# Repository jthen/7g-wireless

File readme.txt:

I've added a few things since my last update.

The first is the ability to "play" a text string as keystrokes on the receiver. So, the keyboards sends the string "this is a message" to the receiver which is then translated into keystrokes. These keystrokes are then sent to the PC as if the user typed "this is a message".

I used this to build a menu system which at the moment is used to set the brightness of the LEDs and the output power of the transmitter. Pressing Func+Esc enters the menu and this is what it currently looks:

[code]
7G wireless
firmware build Jul 30 2013  13:38:18
battery voltage=2.83V
keyboard's been on for 0days 21hour 39min 10sec

what do you want to do?
F1 - change transmitter output power (current 0dBm)
F2 - change LED brightness (current 1)
Esc - exit menu
[/code]
Pressing F1 or F2 then opens a sub-menu which allows changing these values.

The menu shows the current battery voltage. This needs a little tweaking to be more accurate, but it serves it's purpose at the moment. In the next PCB revision, I want to improve the circuit which measures the voltage. I have to dig into the AVR datasheets and look for some examples.

The firmware also has a clock (watch) which starts when the keyboard receives power. That's the "keyboard's been on for..." part of the menu. This clock is used in the sleep system (see below), but can be used as a real clock too.

There is also a LED "driver" thing which allows sequences to be replayed. So, for instance, I can play an LED sequence where 1 LED is on for a while, then 2, then all three. The driver also allows gradual transitions from bright do dim and back, but this still needs some testing, I think there are bugs in it. This can be used for all sorts of indicators.

The bad news: transmitter range sucks! On highest transmitter output power (0dBm) I get a range of 6-8 meters, and on the lowest I get 1-2 meters tops. I've used these modules for other projects, and I've confirmed a range of at least 60 meters. The chip should also be able to send a signal through at least one wall, which is not the case now. This, of course, means there is something wrong. I don't know what causes these, but I'm guessing either the keyboard PCB or my controller PCB are somehow shielding the transmitter. Tests are needed...

I don't do any frequency hopping. The channel is hard-coded at the moment. The transmitter will to re-send the package for for a number of times, or until it gets an acknowledge from the dongle.

The controller does not have any reverse voltage protection. So, reversing the batteries will probably fry the entire circuit. I will have to add this in the next controller revision.

The firmware doesn't do any encryption of the data it sends. This means that it's not too hard to build a circuit that can "listen" and log keystrokes. This can be fixed, of course, but it's not very high on my priority list. I'm not very paranoid...

The firmware puts the keyboard into sleep for a variable duration of time which depends on the time since the last change of the state of the keys. The idea is that while the user is typing, this sleep time will stay relatively short (say, 4ms) and if the user is not typing this interval will gradually increase to a max value (at the moment 71ms). Then, as soon as the user starts typing again, the sleep duration will jump back to the minimal value. Currently the implementaion of this is very crude, and needs more work. I plan to make this configurable so that the user can select if he wants to save power with longer sleeps, or have a more responsive keyboard and drain the batteries quicker. I also thought about making a "deep sleep" mode which puts the keyboard in a state where it will sleep for longer durations (say, 500ms) between matrix scans and wait for a specific key combination to get out of this deep sleep. The idea here is that you want to put the keyboard in deep sleep if you want to transport it, or if you want to lock it. The keyboard could also go into deep sleep if no keys have been pressed for a long time (30 minutes or so) to preserve power.

Because of this sleep system I decided I will not do any debouncing. What's the point of debouncing if I'm already scanning the keyboard matrix every 4ms or longer? Any comments on this?

The source code and the Eagle CAD schematics of the controller PCB are on:

https://code.google.com/p/7g-wireless/

So, that's it for now.

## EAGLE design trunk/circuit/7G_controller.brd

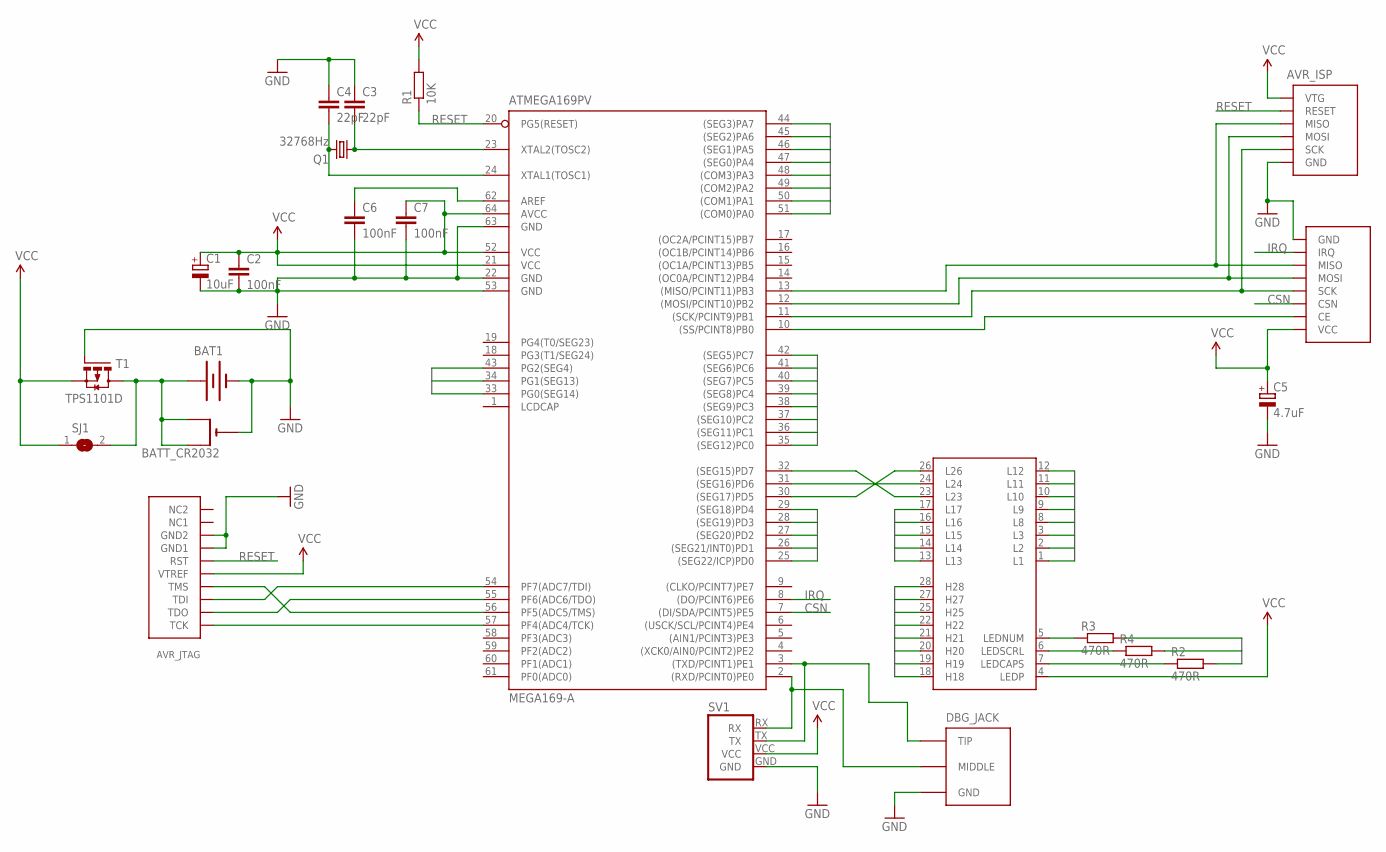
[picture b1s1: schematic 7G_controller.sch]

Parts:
ATMEGA169PV: MEGA169-A; TQFP64
AVR_ISP: AVR-ISP-6SMALL_FP; AVR-ISP-6-SMALL-FP
AVR_JTAG: AVR-JTAG
BAT1: BATTERYPLAIN; BATTERY
BATT_CR2032: CR2032SMT; CR2032-SMD
C1: 10uF; SMC_B
C2, C6, C7: 100nF; C0805
C3, C4: 22pF; C0805
C5: 4.7uF; SMC_B
DBG_JACK: JACK_FEMALE_3.5MMCHEAP; JACK_CHEAP
MTRX_CONN: SS7G_CONNSMD; SS7G_CONN_SMD
NRF24L01: NRF24L01_MOD_NINE_EAGLESGENERIC; NRF24L01_MOD_GENERIC
Q1: 32768Hz; NSK_QUARTZ_CLOCK
R1: 10K; R0805
R2, R3, R4: 470R; R0805
SJ1: SJ
SV1: UART_PORT
T1: TPS1101D; SO8

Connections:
AREF: ATMEGA169PV.62 (AREF), C6.1
CAPS: ATMEGA169PV.43 (PG2(SEG4)), R2.2
CE: ATMEGA169PV.10 ((SS/PCINT8)PB0), NRF24L01.CE
CSN: ATMEGA169PV.7 ((DI/SDA/PCINT5)PE5), NRF24L01.CSN
GND: ATMEGA169PV.22 (GND), ATMEGA169PV.53 (GND), ATMEGA169PV.63 (GND), AVR_ISP.GND, AVR_JTAG.P$2 (GND1), AVR_JTAG.P$10 (GND2), BAT1.-, BATT_CR2032.-, C1.-, C2.2, C3.1, C4.1, C5.-, C6.2, C7.2, DBG_JACK.1 (GND), NRF24L01.GND, SV1.GND, T1.4 (G)
H18: ATMEGA169PV.42 ((SEG5)PC7), MTRX_CONN.18 (H18)
H19: ATMEGA169PV.41 ((SEG6)PC6), MTRX_CONN.19 (H19)
H20: ATMEGA169PV.40 ((SEG7)PC5), MTRX_CONN.20 (H20)
H21: ATMEGA169PV.38 ((SEG9)PC3), MTRX_CONN.21 (H21)
H22: ATMEGA169PV.36 ((SEG11)PC1), MTRX_CONN.22 (H22)
H25: ATMEGA169PV.35 ((SEG12)PC0), MTRX_CONN.25 (H25)
H27: ATMEGA169PV.37 ((SEG10)PC2), MTRX_CONN.27 (H27)
H28: ATMEGA169PV.39 ((SEG8)PC4), MTRX_CONN.28 (H28)
IRQ: ATMEGA169PV.8 ((DO/PCINT6)PE6), NRF24L01.IRQ
L1: ATMEGA169PV.50 ((COM1)PA1), MTRX_CONN.1 (L1)
L2: ATMEGA169PV.48 ((COM3)PA3), MTRX_CONN.2 (L2)
L3: ATMEGA169PV.46 ((SEG1)PA5), MTRX_CONN.3 (L3)
L8: ATMEGA169PV.45 ((SEG2)PA6), MTRX_CONN.8 (L8)
L9: ATMEGA169PV.44 ((SEG3)PA7), MTRX_CONN.9 (L9)
L10: ATMEGA169PV.25 ((SEG22/ICP)PD0), MTRX_CONN.10 (L10)
L11: ATMEGA169PV.26 ((SEG21/INT0)PD1), MTRX_CONN.11 (L11)
L12: ATMEGA169PV.27 ((SEG20)PD2), MTRX_CONN.12 (L12)
L13: ATMEGA169PV.28 ((SEG19)PD3), MTRX_CONN.13 (L13)
L14: ATMEGA169PV.29 ((SEG18)PD4), MTRX_CONN.14 (L14)
L15: ATMEGA169PV.51 ((COM0)PA0), MTRX_CONN.15 (L15)
L16: ATMEGA169PV.49 ((COM2)PA2), MTRX_CONN.16 (L16)
L17: ATMEGA169PV.47 ((SEG0)PA4), MTRX_CONN.17 (L17)
LEDCAPS: MTRX_CONN.7 (LEDCAPS), R2.1
LEDNUM: MTRX_CONN.6 (LEDSCRL), R4.1
LEDSCRL: MTRX_CONN.5 (LEDNUM), R3.1
MISO: ATMEGA169PV.13 ((MISO/PCINT11)PB3), AVR_ISP.MISO, NRF24L01.MISO
MOSI: ATMEGA169PV.12 ((MOSI/PCINT10)PB2), AVR_ISP.MOSI, NRF24L01.MOSI
unnamed: ATMEGA169PV.32 ((SEG15)PD7), MTRX_CONN.23 (L23)
unnamed: BAT1.+, BATT_CR2032.+$1 (+), BATT_CR2032.+$2 (+1), SJ1.2, T1.5 (D), T1.6 (D), T1.7 (D), T1.8 (D)
unnamed: ATMEGA169PV.23 (XTAL2(TOSC2)), C3.2, Q1.1
unnamed: ATMEGA169PV.24 (XTAL1(TOSC1)), C4.2, Q1.4 (2)
unnamed: ATMEGA169PV.30 ((SEG17)PD5), MTRX_CONN.26 (L26)
unnamed: ATMEGA169PV.31 ((SEG16)PD6), MTRX_CONN.24 (L24)
unnamed: ATMEGA169PV.2 ((RXD/PCINT0)PE0), DBG_JACK.4 (MIDDLE), SV1.RX
unnamed: ATMEGA169PV.3 ((TXD/PCINT1)PE1), DBG_JACK.2 (TIP), DBG_JACK.3 (TIP), SV1.TX
NUML: ATMEGA169PV.33 (PG0(SEG14)), R3.2
RESET: ATMEGA169PV.20 (PG5(RESET)), AVR_ISP.RESET, AVR_JTAG.P$6 (RST), R1.1
SCK: ATMEGA169PV.11 ((SCK/PCINT9)PB1), AVR_ISP.SCK, NRF24L01.SCK
SCRL: ATMEGA169PV.34 (PG1(SEG13)), R4.2
TCK: ATMEGA169PV.57 (PF4(ADC4/TCK)), AVR_JTAG.P$1 (TCK)
TDI: ATMEGA169PV.54 (PF7(ADC7/TDI)), AVR_JTAG.P$9 (TDI)
TDO: ATMEGA169PV.55 (PF6(ADC6/TDO)), AVR_JTAG.P$3 (TDO)
TMS: ATMEGA169PV.56 (PF5(ADC5/TMS)), AVR_JTAG.P$5 (TMS)
VCC: ATMEGA169PV.21 (VCC), ATMEGA169PV.52 (VCC), ATMEGA169PV.64 (AVCC), AVR_ISP.VCC (VTG), AVR_JTAG.P$4 (VTREF), C1.+, C2.1, C5.+, C7.1, MTRX_CONN.4 (LEDP), NRF24L01.+3.3V (VCC), R1.2, SJ1.1, SV1.VCC, T1.1 (S), T1.2 (S), T1.3 (S)

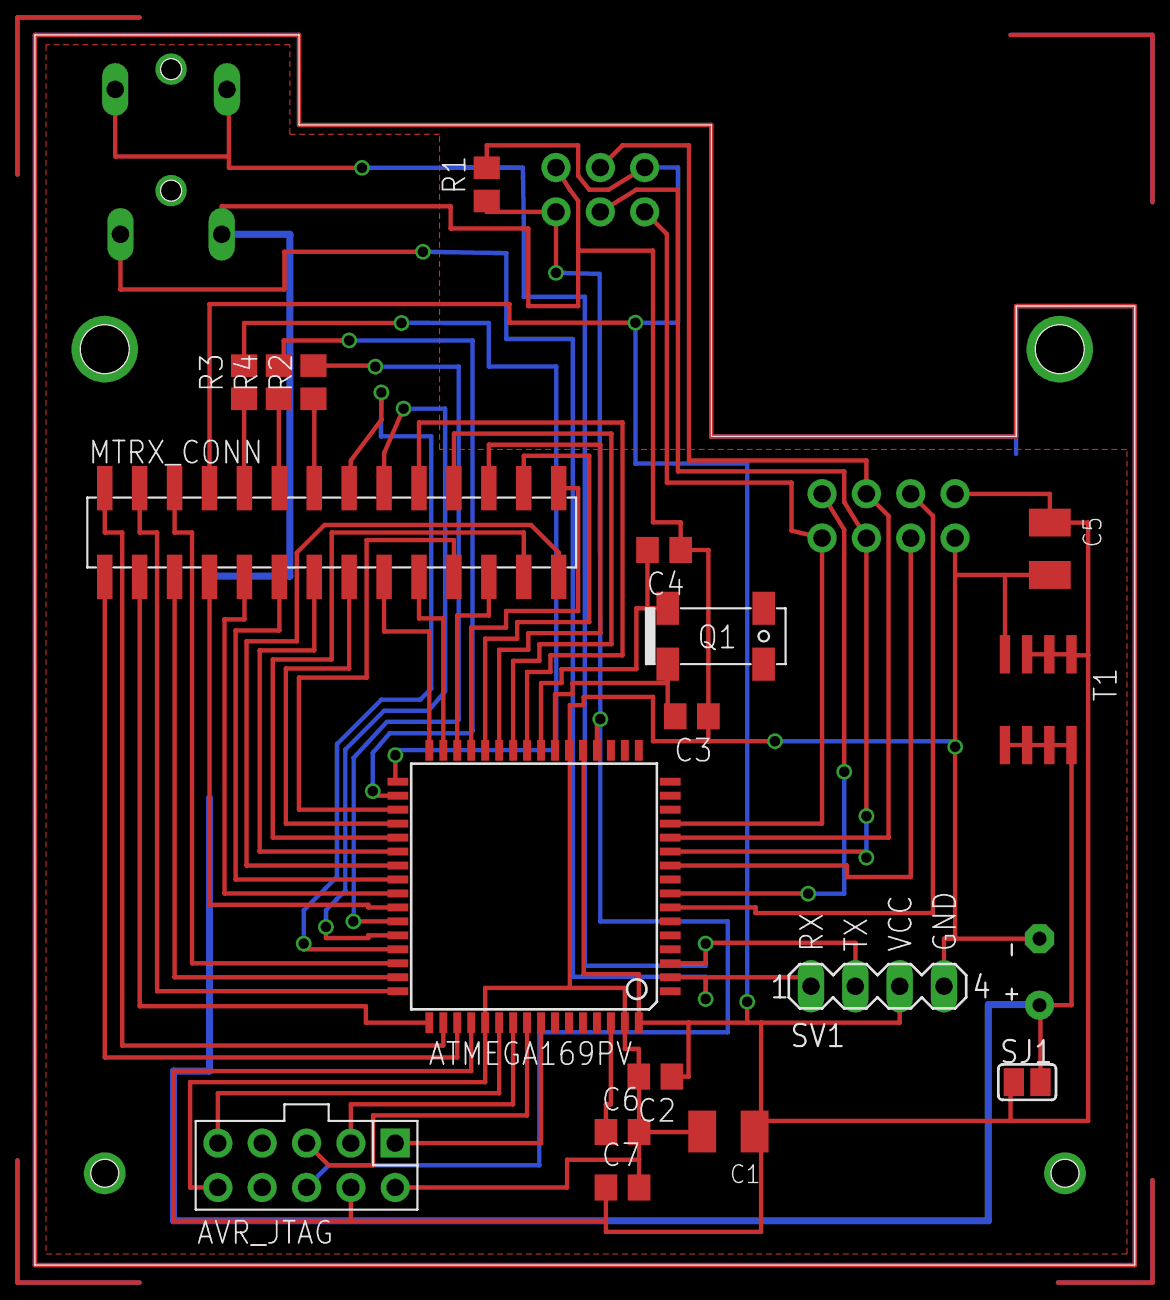
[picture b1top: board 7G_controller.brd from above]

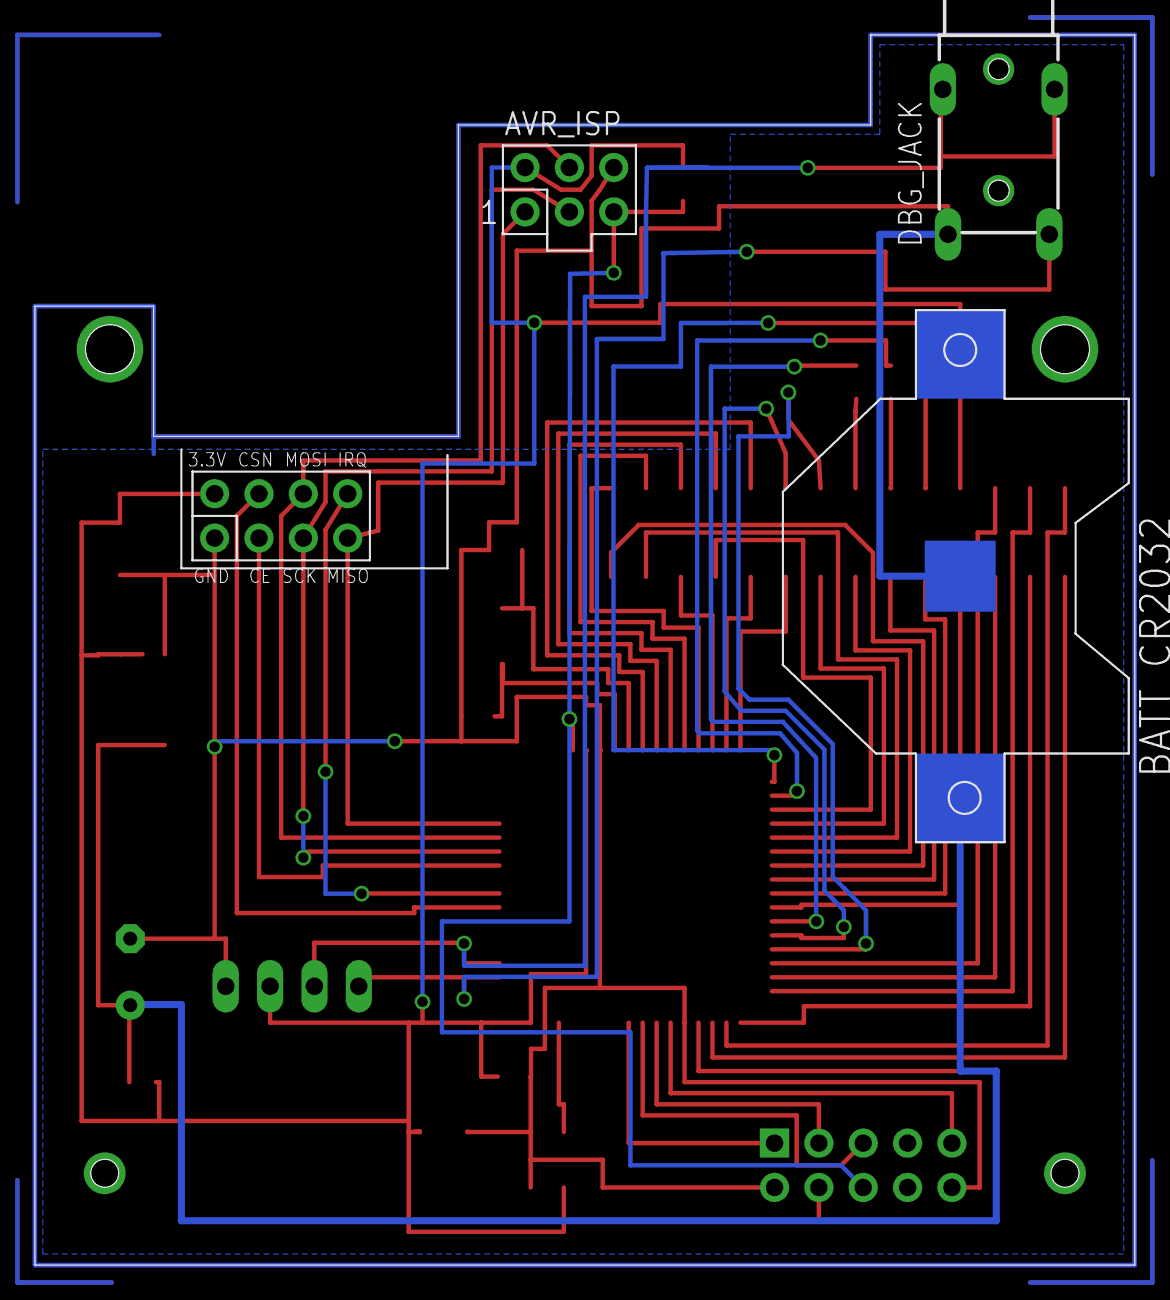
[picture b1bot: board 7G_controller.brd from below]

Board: 2 copper layers, 63.0 x 70.5 mm, 23 parts (4 on the bottom side), 49 nets.

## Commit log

2013-07-25 Initial directory structure.
2013-08-27 fixed the LED sequence replay bugs
2013-08-27 renamed avr_serial -> avrdbg
2013-12-26 - separated source of dongle and controller into separate directories plus common - added support to the nRF library for nRF24LU1+ and sdcc
2013-12-29 CR2032 holder
2014-01-02 added counting RF packets (total/retransmit/lost) to menu
2014-01-02 finished adding the CR2032 battery holder
2014-02-21 started nRF dongle
2014-02-21 all is compiling
2014-02-22 nRF24LU1+ dongle is working. Needs testing and cosmetic changes.
2014-02-24 made the RF connect a little more reliable. fixed the lag menu of the menu system with full speed dongles
2014-02-28 in the middle of debugging text_message.c
2014-02-28 text messages should work reliably in noisy environments. added nRF UART debug output library
2014-03-01 added Func+KeypadPlus and Func+KeypadMinus for power increase and decrease
2014-03-02 changed channel number from 2 to 101
2014-03-29 fixed compile problem with avr-gcc 4.8.1. Still getting warnings for misspelled signal vector.
2014-03-30 tweaks for different targets
2014-03-30 nRF24LE1 and nRF24LU1 are a little different
2014-03-30 switched to external mcu-lib
2015-07-13 Migrating wiki contents from Google Code

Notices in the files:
parts and their libraries:
SparkFun: Licensing: CC v3.0 Share-Alike You are welcome to use this library for commercial purposes.
